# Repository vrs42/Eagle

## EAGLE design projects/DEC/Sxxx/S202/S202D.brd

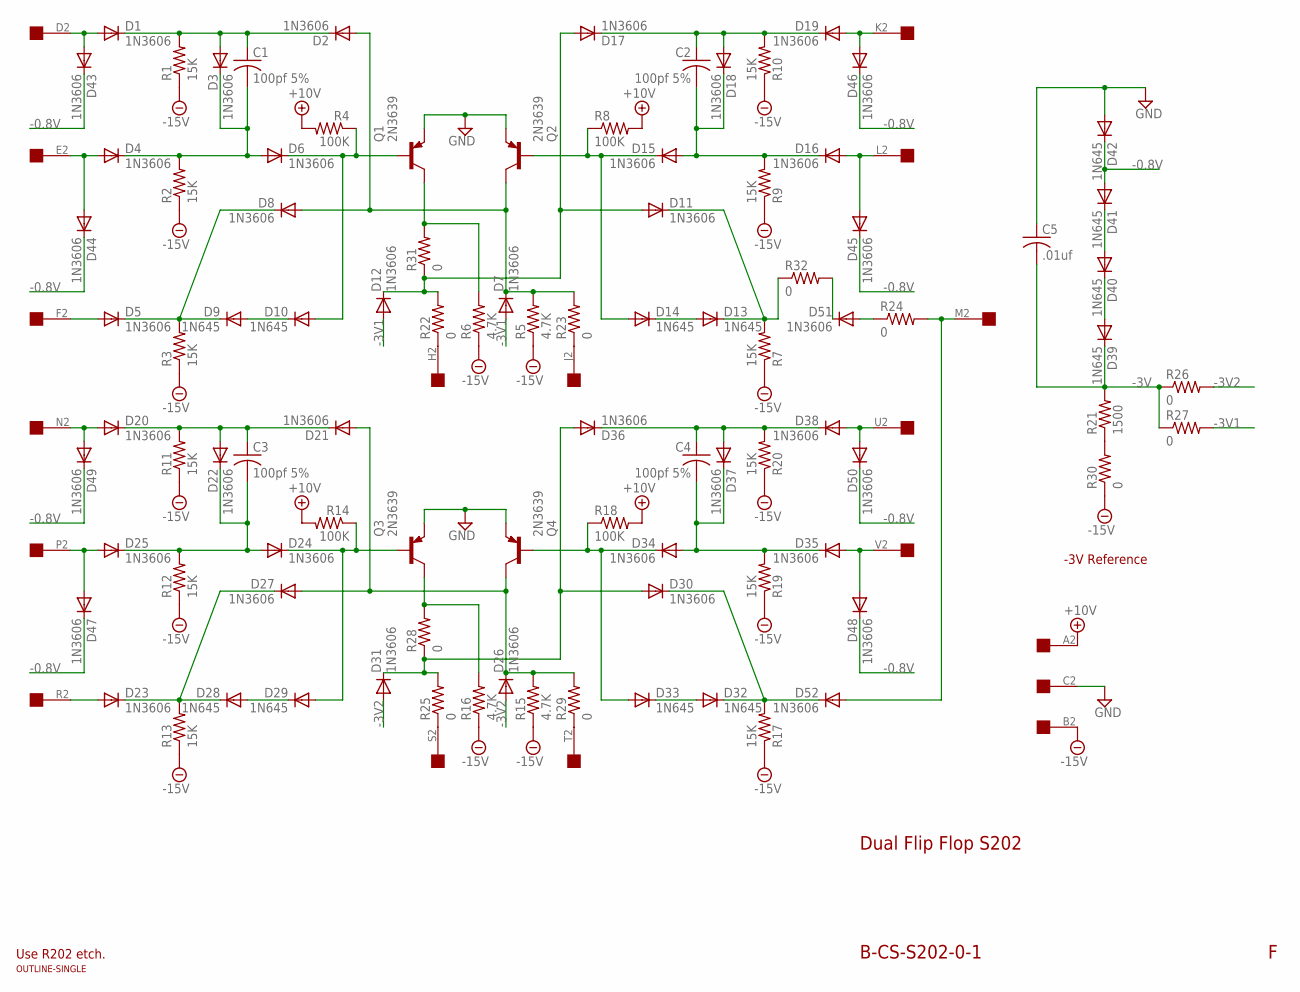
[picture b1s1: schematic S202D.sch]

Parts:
C1, C2, C3, C4: 100pf 5%; C050-025X075
C5: .01uf; C050-025X075
D1, D2, D3, D4, D5, D6, D7, D8, D11, D12, D15, D16, D17, D18, D19, D20, D21, D22, D23, D24, D25, D26, D27, D30, D31, D34, D35, D36, D37, D38, D43, D44, D45, D46, D47, D48, D49, D50, D51, D52: 1N3606; DO35-10
D9, D10, D13, D14, D28, D29, D32, D33, D39, D40, D41, D42: 1N645; DO35-10
Q1, Q2, Q3, Q4: 2N3639; TO39
R1, R2, R3, R7, R9, R10, R11, R12, R13, R17, R19, R20: 15K; 0207/10
R4, R8, R14, R18: 100K; 0207/10
R5, R6, R15, R16: 4.7K; 0207/10
R21: 1500; 0207/10
R22, R23, R24, R25, R26, R27, R28, R29, R30, R31, R32: 0; 0207/10
U$1: OUTLINE-SINGLE; SINGLE
U$2: EDGE-1; EDGE-CON1

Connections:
+10V: R4.2, R8.2, R14.2, R18.2, U$2.A2
-0.8V: D41.A, D42.C, D43.C, D44.C, D45.C, D46.C, D47.C, D48.C, D49.C, D50.C
-3V: C5.2, D39.C, R21.2, R26.1, R27.1
-3V1: D7.A, D12.A, R27.2
-3V2: D26.A, D31.A, R26.2
-15V: R1.1, R2.1, R3.1, R5.1, R6.1, R7.1, R9.1, R10.1, R11.1, R12.1, R13.1, R15.1, R16.1, R17.1, R19.1, R20.1, R30.1, U$2.B2
GND: C5.1, D42.A, Q1.1 (E), Q2.1 (E), Q3.1 (E), Q4.1 (E), U$2.C2
H: D11.A, D12.C, D17.A, R22.2, R31.1
J: D2.A, D7.C, D8.A, Q2.3 (C), R5.2, R23.2
unnamed: Q3.3 (C), R16.2, R28.2
unnamed: C2.1, D17.C, D18.A, D19.C, R10.2
unnamed: C1.2, D3.C, D4.C, D6.A, R2.2
unnamed: D1.A, D43.A, U$2.D2
unnamed: D4.A, D44.A, U$2.E2
unnamed: D13.A, D14.C
unnamed: D19.A, D46.A, U$2.K2
unnamed: C2.2, D15.A, D16.C, D18.C, R9.2
unnamed: D5.C, D8.C, D9.C, R3.2
unnamed: D5.A, U$2.F2
unnamed: D16.A, D45.A, U$2.L2
unnamed: D11.C, D13.C, R7.2, R32.1
unnamed: D40.A, D41.C
unnamed: D6.C, D10.A, Q1.2 (B), R4.1
unnamed: D52.A, R24.2, U$2.M2
unnamed: D39.A, D40.C
unnamed: D14.A, D15.C, Q2.2 (B), R8.1
unnamed: C3.1, D20.C, D21.C, D22.A, R11.2
unnamed: D28.A, D29.C
unnamed: D20.A, D49.A, U$2.N2
unnamed: C3.2, D22.C, D24.A, D25.C, R12.2
unnamed: C1.1, D1.C, D2.C, D3.A, R1.2
unnamed: D9.A, D10.C
unnamed: D25.A, D47.A, U$2.P2
unnamed: D23.C, D27.C, D28.C, R13.2
unnamed: D23.A, U$2.R2
unnamed: D24.C, D29.A, Q3.2 (B), R14.1
unnamed: C4.1, D36.C, D37.A, D38.C, R20.2
unnamed: D32.A, D33.C
unnamed: D38.A, D50.A, U$2.U2
unnamed: C4.2, D34.A, D35.C, D37.C, R19.2
unnamed: D35.A, D48.A, U$2.V2
unnamed: R22.1, U$2.H2
unnamed: D33.A, D34.C, Q4.2 (B), R18.1
unnamed: D30.C, D32.C, D52.C, R17.2
unnamed: R23.1, U$2.J2
unnamed: D51.A, R24.1
unnamed: R25.1, U$2.S2
unnamed: R29.1, U$2.T2
unnamed: R21.1, R30.2
unnamed: Q1.3 (C), R6.2, R31.2
unnamed: D51.C, R32.2
S: D30.A, D31.C, D36.A, R25.2, R28.1
T: D21.A, D26.C, D27.A, Q4.3 (C), R15.2, R29.2

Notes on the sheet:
Dual Flip Flop S202
B-CS-S202-0-1
-3V Reference
Use R202 etch.

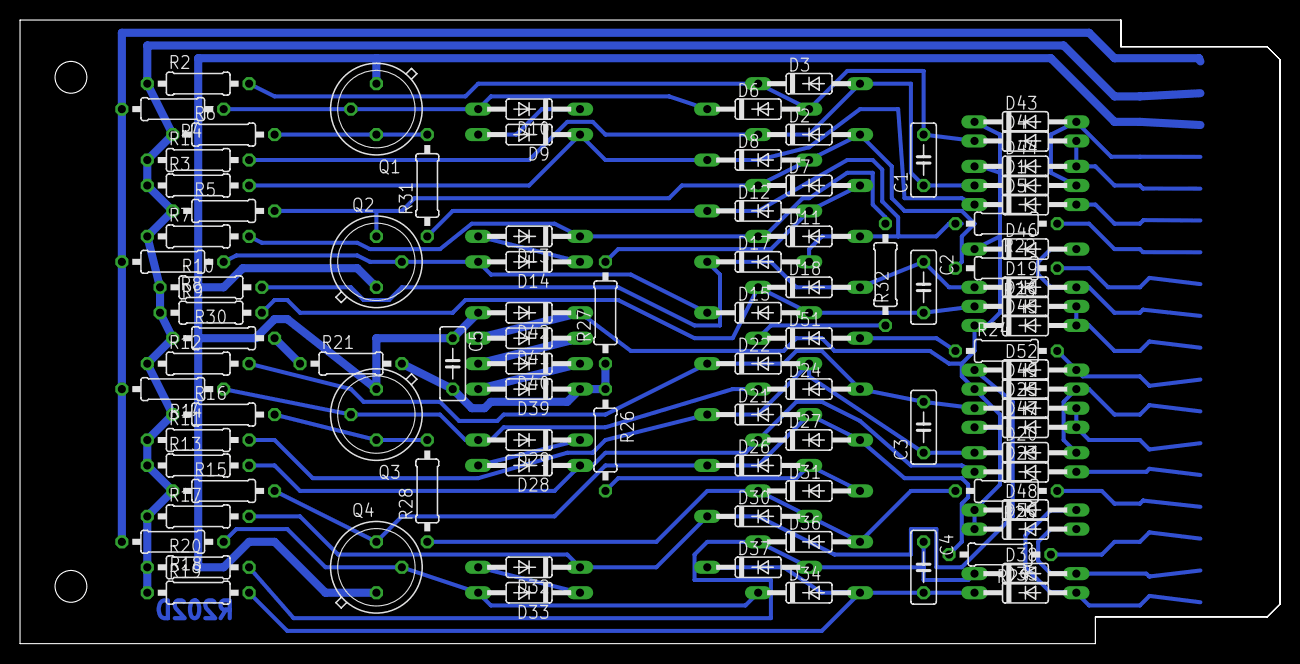
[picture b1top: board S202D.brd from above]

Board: 2 copper layers, 125.7 x 62.2 mm, 95 parts (0 on the bottom side), 53 nets.

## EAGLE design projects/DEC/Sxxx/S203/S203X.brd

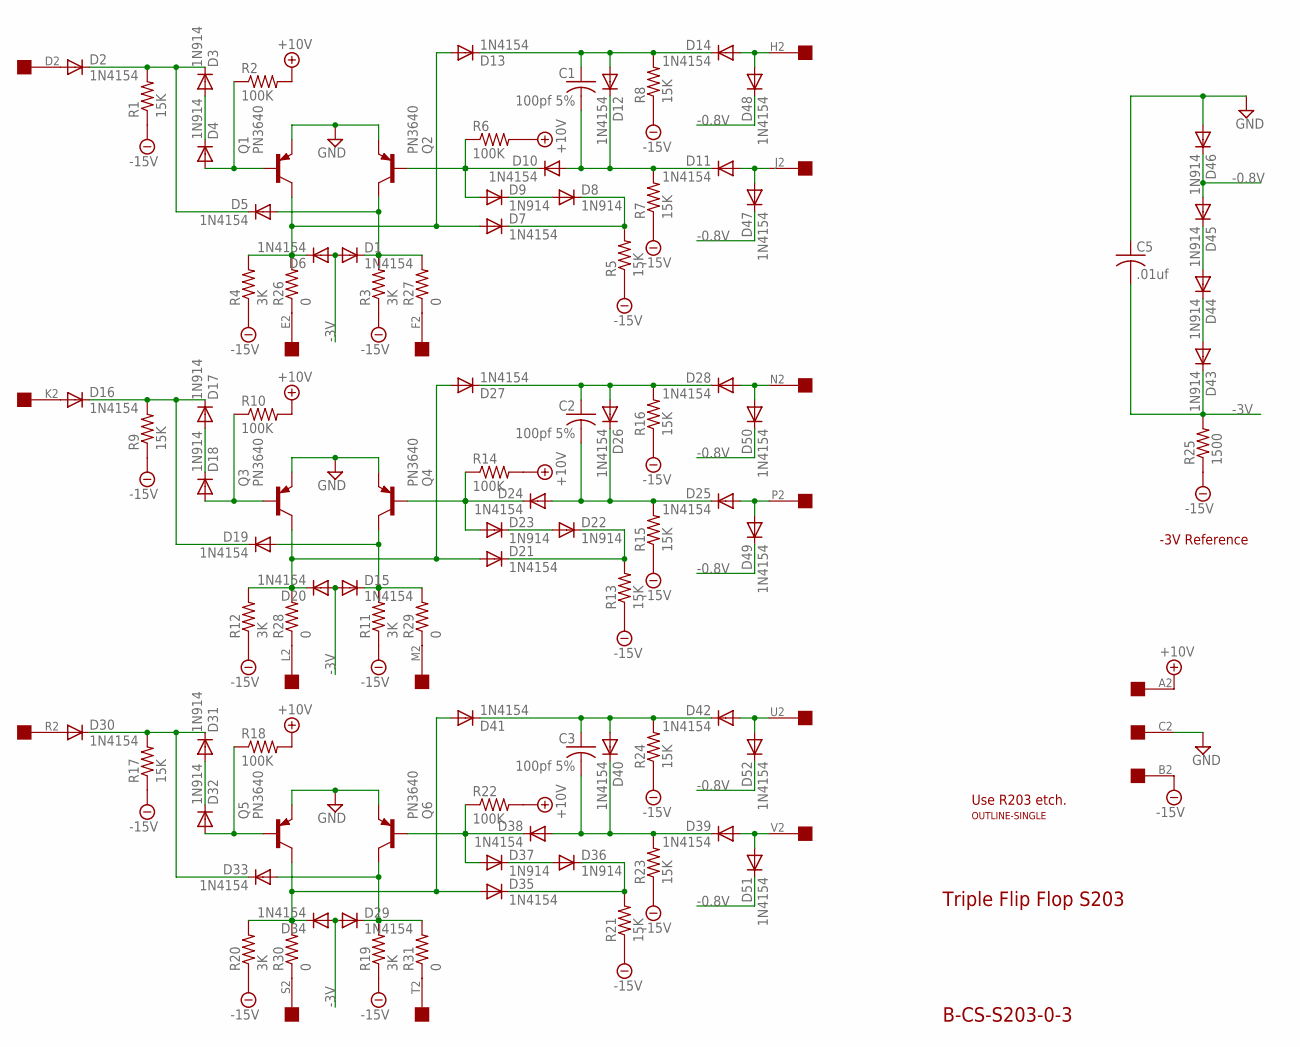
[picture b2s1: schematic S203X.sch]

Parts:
C1, C2, C3: 100pf 5%; C050-025X075
C5: .01uf; C050-025X075
D1, D2, D5, D6, D7, D10, D11, D12, D13, D14, D15, D16, D19, D20, D21, D24, D25, D26, D27, D28, D29, D30, D33, D34, D35, D38, D39, D40, D41, D42, D47, D48, D49, D50, D51, D52: 1N4154; DO35-10
D3, D4, D8, D9, D17, D18, D22, D23, D31, D32, D36, D37, D43, D44, D45, D46: 1N914; DO35-10
Q1, Q2, Q3, Q4, Q5, Q6: PN3640; TO39
R1, R5, R7, R8, R9, R13, R15, R16, R17, R21, R23, R24: 15K; 0207/10
R2, R6, R10, R14, R18, R22: 100K; 0207/10
R3, R4, R11, R12, R19, R20: 3K; 0207/10
R25: 1500; 0207/10
R26, R27, R28, R29, R30, R31: 0; 0207/10
U$1: OUTLINE-SINGLE; SINGLE
U$2: EDGE-1; EDGE-CON1

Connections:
+10V: R2.2, R6.2, R10.2, R14.2, R18.2, R22.2, U$2.A2
-0.8V: D45.A, D46.C, D47.C, D48.C, D49.C, D50.C, D51.C, D52.C
-3V: C5.2, D1.A, D6.A, D15.A, D20.A, D29.A, D34.A, D43.C, R25.2
-15V: R1.1, R3.1, R4.1, R5.1, R7.1, R8.1, R9.1, R11.1, R12.1, R13.1, R15.1, R16.1, R17.1, R19.1, R20.1, R21.1, R23.1, R24.1, R25.1, U$2.B2
E: D6.C, D7.A, D13.A, Q1.3 (C), R4.2, R26.2
F: D1.C, D5.A, Q2.3 (C), R3.2, R27.2
GND: C5.1, D46.A, Q1.1 (E), Q2.1 (E), Q3.1 (E), Q4.1 (E), Q5.1 (E), Q6.1 (E), U$2.C2
L: D20.C, D21.A, D27.A, Q3.3 (C), R12.2, R28.2
M: D15.C, D19.A, Q4.3 (C), R11.2, R29.2
unnamed: D31.A, D32.C
unnamed: C1.1, D12.A, D13.C, D14.C, R8.2
unnamed: D30.C, D31.C, D33.C, R17.2
unnamed: D30.A, U$2.R2
unnamed: D8.A, D9.C
unnamed: D14.A, D48.A, U$2.H2
unnamed: C1.2, D10.A, D11.C, D12.C, R7.2
unnamed: D2.C, D3.C, D5.C, R1.2
unnamed: D2.A, U$2.D2
unnamed: D11.A, D47.A, U$2.J2
unnamed: D7.C, D8.C, R5.2
unnamed: D44.A, D45.C
unnamed: D4.A, Q1.2 (B), R2.1
unnamed: D32.A, Q5.2 (B), R18.1
unnamed: D43.A, D44.C
unnamed: D9.A, D10.C, Q2.2 (B), R6.1
unnamed: C3.1, D40.A, D41.C, D42.C, R24.2
unnamed: D17.A, D18.C
unnamed: D36.A, D37.C
unnamed: D42.A, D52.A, U$2.U2
unnamed: C3.2, D38.A, D39.C, D40.C, R23.2
unnamed: D3.A, D4.C
unnamed: D39.A, D51.A, U$2.V2
unnamed: D16.C, D17.C, D19.C, R9.2
unnamed: D16.A, U$2.K2
unnamed: D18.A, Q3.2 (B), R10.1
unnamed: C2.1, D26.A, D27.C, D28.C, R16.2
unnamed: D22.A, D23.C
unnamed: D28.A, D50.A, U$2.N2
unnamed: C2.2, D24.A, D25.C, D26.C, R15.2
unnamed: D25.A, D49.A, U$2.P2
unnamed: R26.1, U$2.E2
unnamed: D23.A, D24.C, Q4.2 (B), R14.1
unnamed: D21.C, D22.C, R13.2
unnamed: R27.1, U$2.F2
unnamed: D37.A, D38.C, Q6.2 (B), R22.1
unnamed: R28.1, U$2.L2
unnamed: R29.1, U$2.M2
unnamed: D35.C, D36.C, R21.2
unnamed: R30.1, U$2.S2
unnamed: R31.1, U$2.T2
S: D34.C, D35.A, D41.A, Q5.3 (C), R20.2, R30.2
T: D29.C, D33.A, Q6.3 (C), R19.2, R31.2

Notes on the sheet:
Triple Flip Flop S203
B-CS-S203-0-3
-3V Reference
Use R203 etch.

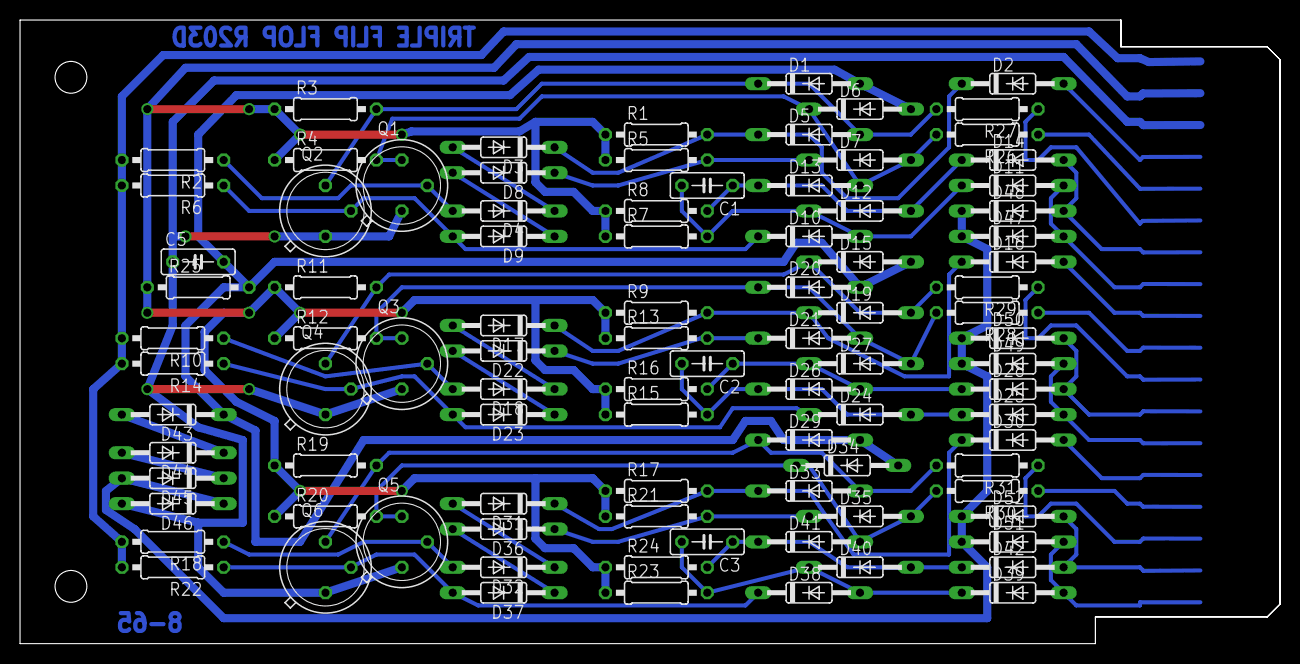
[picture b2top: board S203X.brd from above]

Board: 2 copper layers, 125.7 x 62.2 mm, 95 parts (0 on the bottom side), 52 nets.

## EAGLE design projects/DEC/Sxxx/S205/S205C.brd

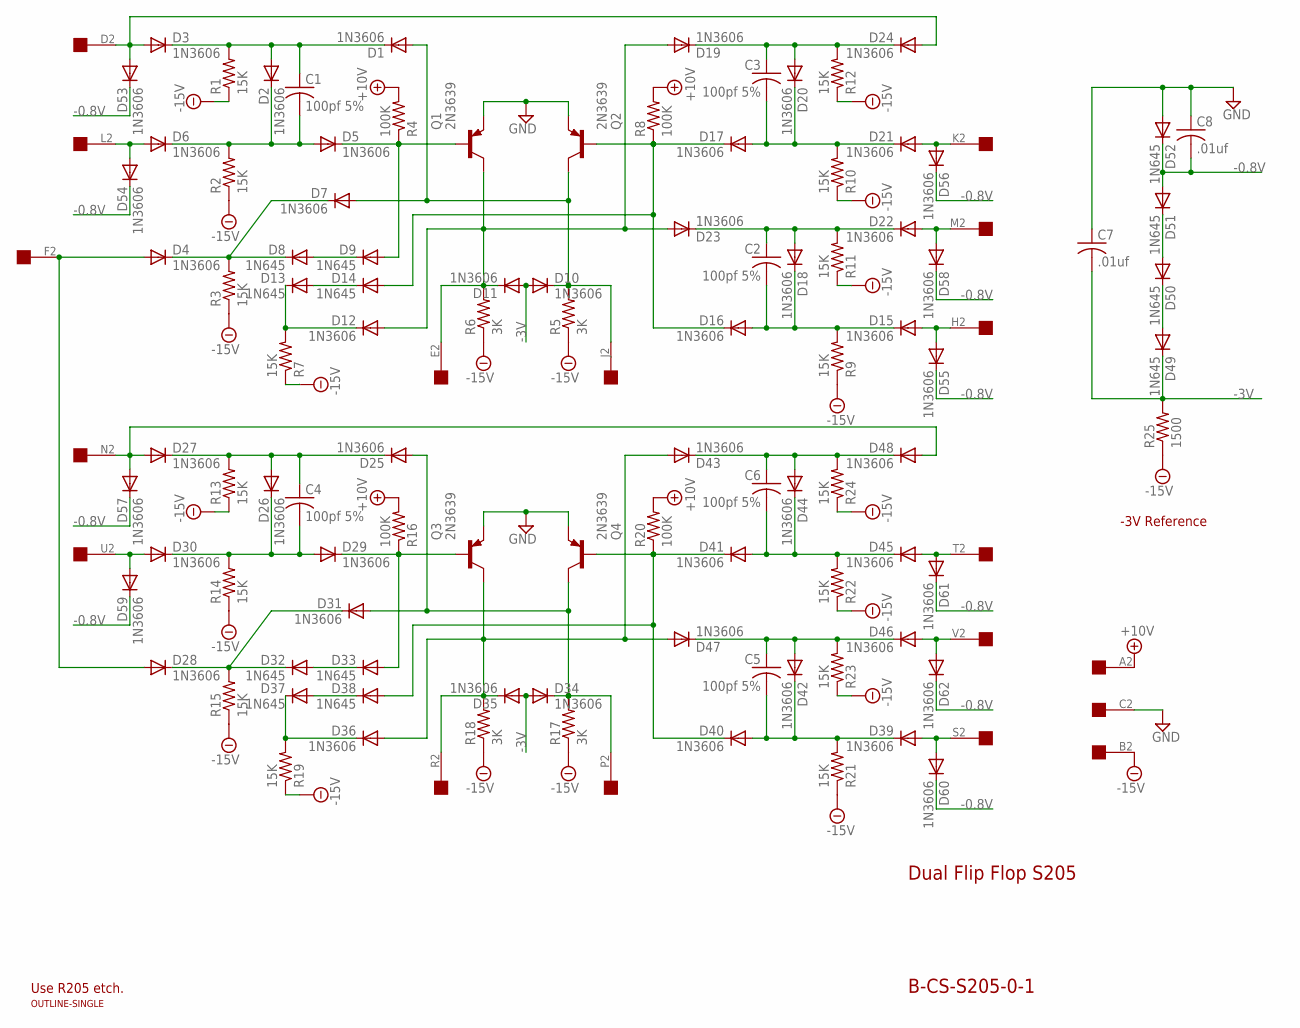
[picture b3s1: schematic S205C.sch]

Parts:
C1, C2, C3, C4, C5, C6: 100pf 5%; C050-025X075
C7, C8: .01uf; C050-025X075
D1, D2, D3, D4, D5, D6, D7, D10, D11, D12, D15, D16, D17, D18, D19, D20, D21, D22, D23, D24, D25, D26, D27, D28, D29, D30, D31, D34, D35, D36, D39, D40, D41, D42, D43, D44, D45, D46, D47, D48, D53, D54, D55, D56, D57, D58, D59, D60, D61, D62: 1N3606; DO35-10
D8, D9, D13, D14, D32, D33, D37, D38, D49, D50, D51, D52: 1N645; DO35-10
Q1, Q2, Q3, Q4: 2N3639; TO39
R1, R2, R3, R7, R9, R10, R11, R12, R13, R14, R15, R19, R21, R22, R23, R24: 15K; 0207/10
R4, R8, R16, R20: 100K; 0207/10
R5, R6, R17, R18: 3K; 0207/10
R25: 1500; 0207/10
U$1: OUTLINE-SINGLE; SINGLE
U$2: EDGE-1; EDGE-CON1

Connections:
+10V: R4.2, R8.2, R16.2, R20.2, U$2.A2
-0.8V: C8.2, D51.A, D52.C, D53.C, D54.C, D55.C, D56.C, D57.C, D58.C, D59.C, D60.C, D61.C, D62.C
-3V: C7.2, D10.A, D11.A, D34.A, D35.A, D49.C, R25.2
-15V: R1.1, R2.1, R3.1, R5.1, R6.1, R7.1, R9.1, R10.1, R11.1, R12.1, R13.1, R14.1, R15.1, R17.1, R18.1, R19.1, R21.1, R22.1, R23.1, R24.1, R25.1, U$2.B2
E: D11.C, D12.A, D19.A, D23.A, Q1.3 (C), R6.2, U$2.E2
GND: C7.1, C8.1, D52.A, Q1.1 (E), Q2.1 (E), Q3.1 (E), Q4.1 (E), U$2.C2
J: D1.A, D7.A, D10.C, Q2.3 (C), R5.2, U$2.J2
unnamed: C4.1, D25.C, D26.A, D27.C, R13.2
unnamed: C3.1, D19.C, D20.A, D24.C, R12.2
unnamed: C1.2, D2.C, D5.A, D6.C, R2.2
unnamed: D3.A, D24.A, D53.A, U$2.D2
unnamed: D6.A, D54.A, U$2.L2
unnamed: D13.A, D14.C
unnamed: D32.A, D33.C
unnamed: C3.2, D17.A, D20.C, D21.C, R10.2
unnamed: D4.C, D7.C, D8.C, R3.2
unnamed: D4.A, D28.A, U$2.F2
unnamed: D21.A, D56.A, U$2.K2
unnamed: D12.C, D13.C, R7.2
unnamed: D50.A, D51.C
unnamed: D5.C, D9.A, Q1.2 (B), R4.1
unnamed: C4.2, D26.C, D29.A, D30.C, R14.2
unnamed: D49.A, D50.C
unnamed: D14.A, D16.C, D17.C, Q2.2 (B), R8.1
unnamed: D30.A, D59.A, U$2.U2
unnamed: D28.C, D31.C, D32.C, R15.2
unnamed: D29.C, D33.A, Q3.2 (B), R16.1
unnamed: C1.1, D1.C, D2.A, D3.C, R1.2
unnamed: D8.A, D9.C
unnamed: C6.1, D43.C, D44.A, D48.C, R24.2
unnamed: D37.A, D38.C
unnamed: C6.2, D41.A, D44.C, D45.C, R22.2
unnamed: D45.A, D61.A, U$2.T2
unnamed: C2.1, D18.A, D22.C, D23.C, R11.2
unnamed: D38.A, D40.C, D41.C, Q4.2 (B), R20.1
unnamed: D22.A, D58.A, U$2.M2
unnamed: C2.2, D15.C, D16.A, D18.C, R9.2
unnamed: D15.A, D55.A, U$2.H2
unnamed: D36.C, D37.C, R19.2
unnamed: C5.1, D42.A, D46.C, D47.C, R23.2
unnamed: D46.A, D62.A, U$2.V2
unnamed: C5.2, D39.C, D40.A, D42.C, R21.2
unnamed: D39.A, D60.A, U$2.S2
unnamed: D27.A, D48.A, D57.A, U$2.N2
P: D25.A, D31.A, D34.C, Q4.3 (C), R17.2, U$2.P2
R: D35.C, D36.A, D43.A, D47.A, Q3.3 (C), R18.2, U$2.R2

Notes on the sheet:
Dual Flip Flop S205
B-CS-S205-0-1
-3V Reference
Use R205 etch.

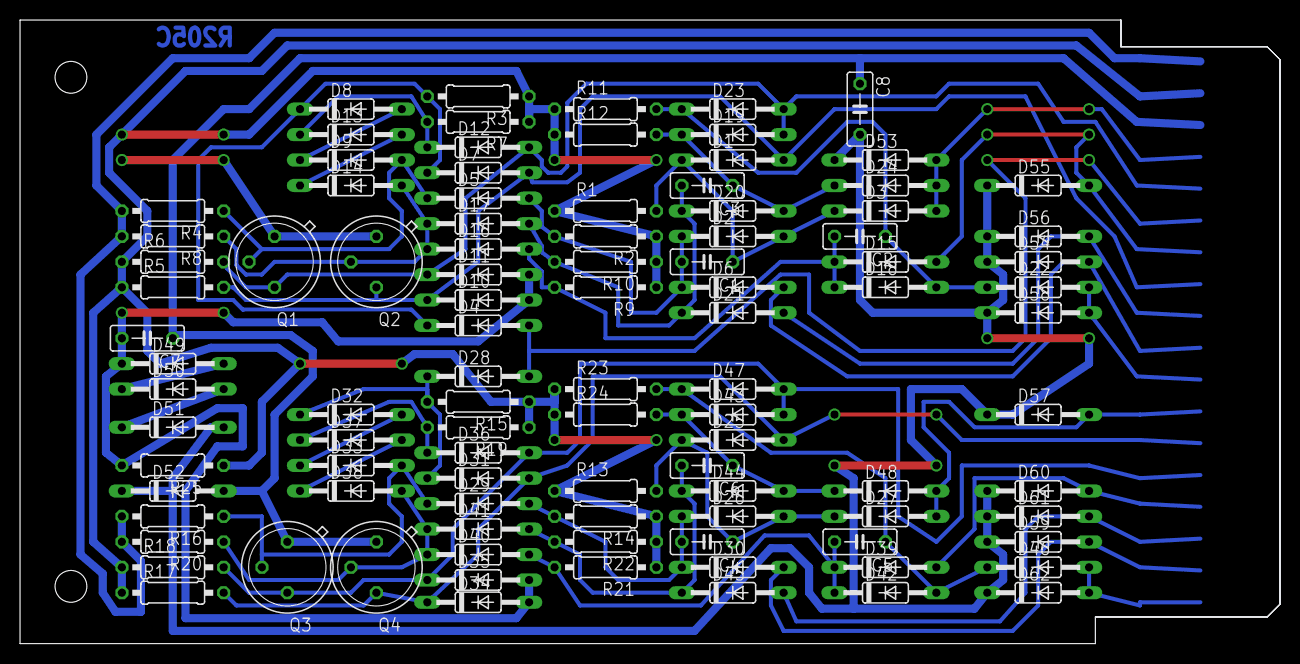
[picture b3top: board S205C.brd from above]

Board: 2 copper layers, 125.7 x 62.2 mm, 101 parts (0 on the bottom side), 46 nets.
